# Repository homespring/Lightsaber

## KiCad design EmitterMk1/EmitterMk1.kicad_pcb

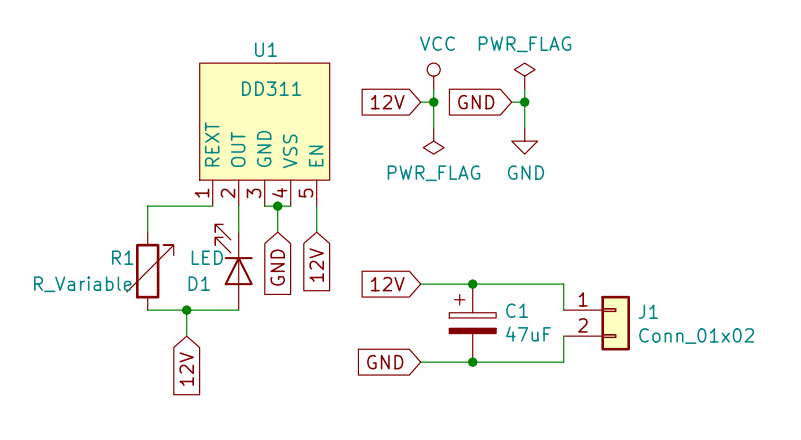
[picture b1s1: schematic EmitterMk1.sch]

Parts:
C1: 47uF; CP_Radial_D5.0mm_P2.00mm
D1: LED; LED_1W_3W_R8
J1: Conn_01x02; PinHeader_1x02_P2.54mm_Vertical
R1: R_Variable; Potentiometer_TM3FJ_3x3.65mm
U1: DD311; TO-252-5_TabPin3

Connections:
12V: C1.1, D1.2 (A), J1.1, R1.2, U1.5 (EN)
GND: C1.2, J1.2, U1.3 (GND), U1.4 (VSS)
unnamed: D1.1 (K), U1.2 (OUT)
unnamed: R1.1, U1.1 (REXT)

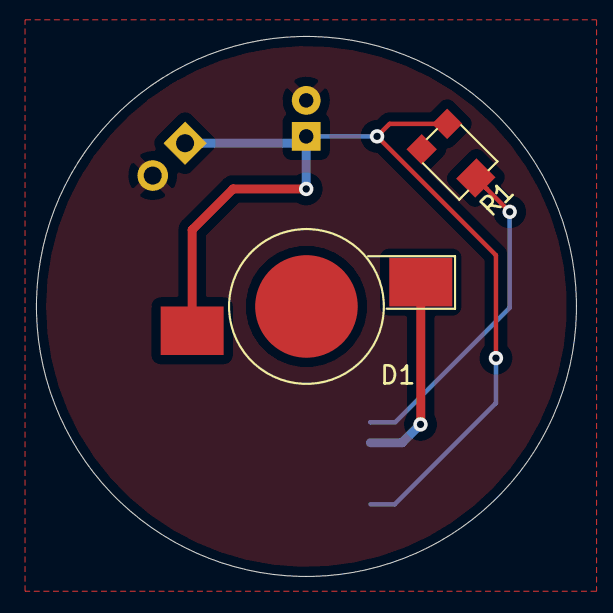
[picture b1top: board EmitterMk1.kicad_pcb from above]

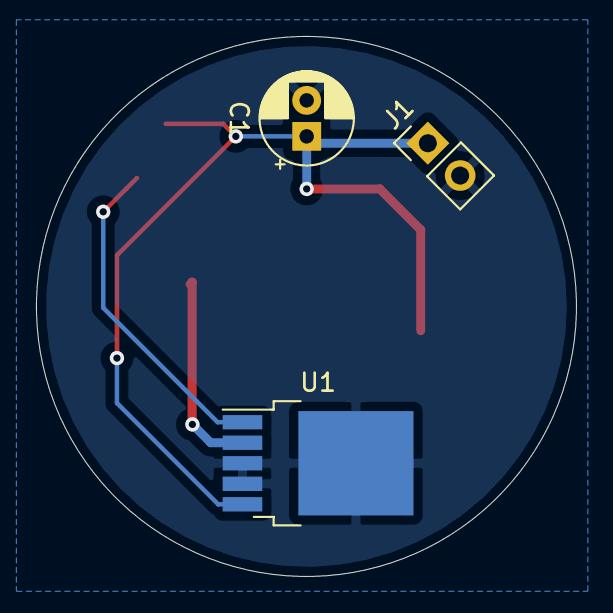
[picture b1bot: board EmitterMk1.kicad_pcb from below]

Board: 2 copper layers, 30.0 x 30.0 mm, 5 parts (3 on the bottom side), 4 nets.

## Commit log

2019-10-10 init commit
